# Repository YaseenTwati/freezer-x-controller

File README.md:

# Freezer X Controller

This project is a custom controller board built to replace the original controller of my freezer that stopped working. It is based on the Arduino Pro Micro and operates by reading the 10K NTC in the fridge and controlling the compressor relay.
**Note:** This controller *does not* replace the built-in compressor relay; instead, it uses an additional relay to control it.

[Dev Log Video](https://www.youtube.com/watch?v=zM9pKCJK8DQ)

**Disclaimer:** I do not recommend anyone build or use this as-is. Use it as a reference only. This was built for my specific use case, and it may or may not meet your needs.

<div style="display: flex; flex-direction: row; justify-content: space-around">

</div>

### Features:
- Interactive menu with configurable settings (target temp, dead time, max temp, hysteresis, etc.)
- Compressor dead time (minimum time the compressor must remain off before turning on again)
- Compressor overheating protection
- NTC short/disconnection handling (min/max temp)
- Raw SD card data logging
- Startup delay

### Important Notes:
1. **RTC Clock is disabled in the code**
   The RTC clock was originally intended to add real-time data to the logs. However, the IC used proved unreliable, so the RTC functionality was disabled in the code to save space.

2. **USB Serial / CDC**
   The USB CDC peripheral is disabled in the PlatformIO configuration to save flash storage space. This means `Serial.print()` cannot be used, **and the board needs to be manually reset during code uploads.**

   You can likely re-enable it now that the RTC is disabled, as there should be enough space available.

3. **SD Card Raw Data**
   Data is logged directly to the SD card without a filesystem by sending raw SPI commands. This approach was taken as an extreme storage-saving measure since most SD card libraries require too much space.
   [I wrote a blog post about this topic if you're interested](https://yaseen.ly/writing-data-to-sdcards-without-a-filesystem-spi/).

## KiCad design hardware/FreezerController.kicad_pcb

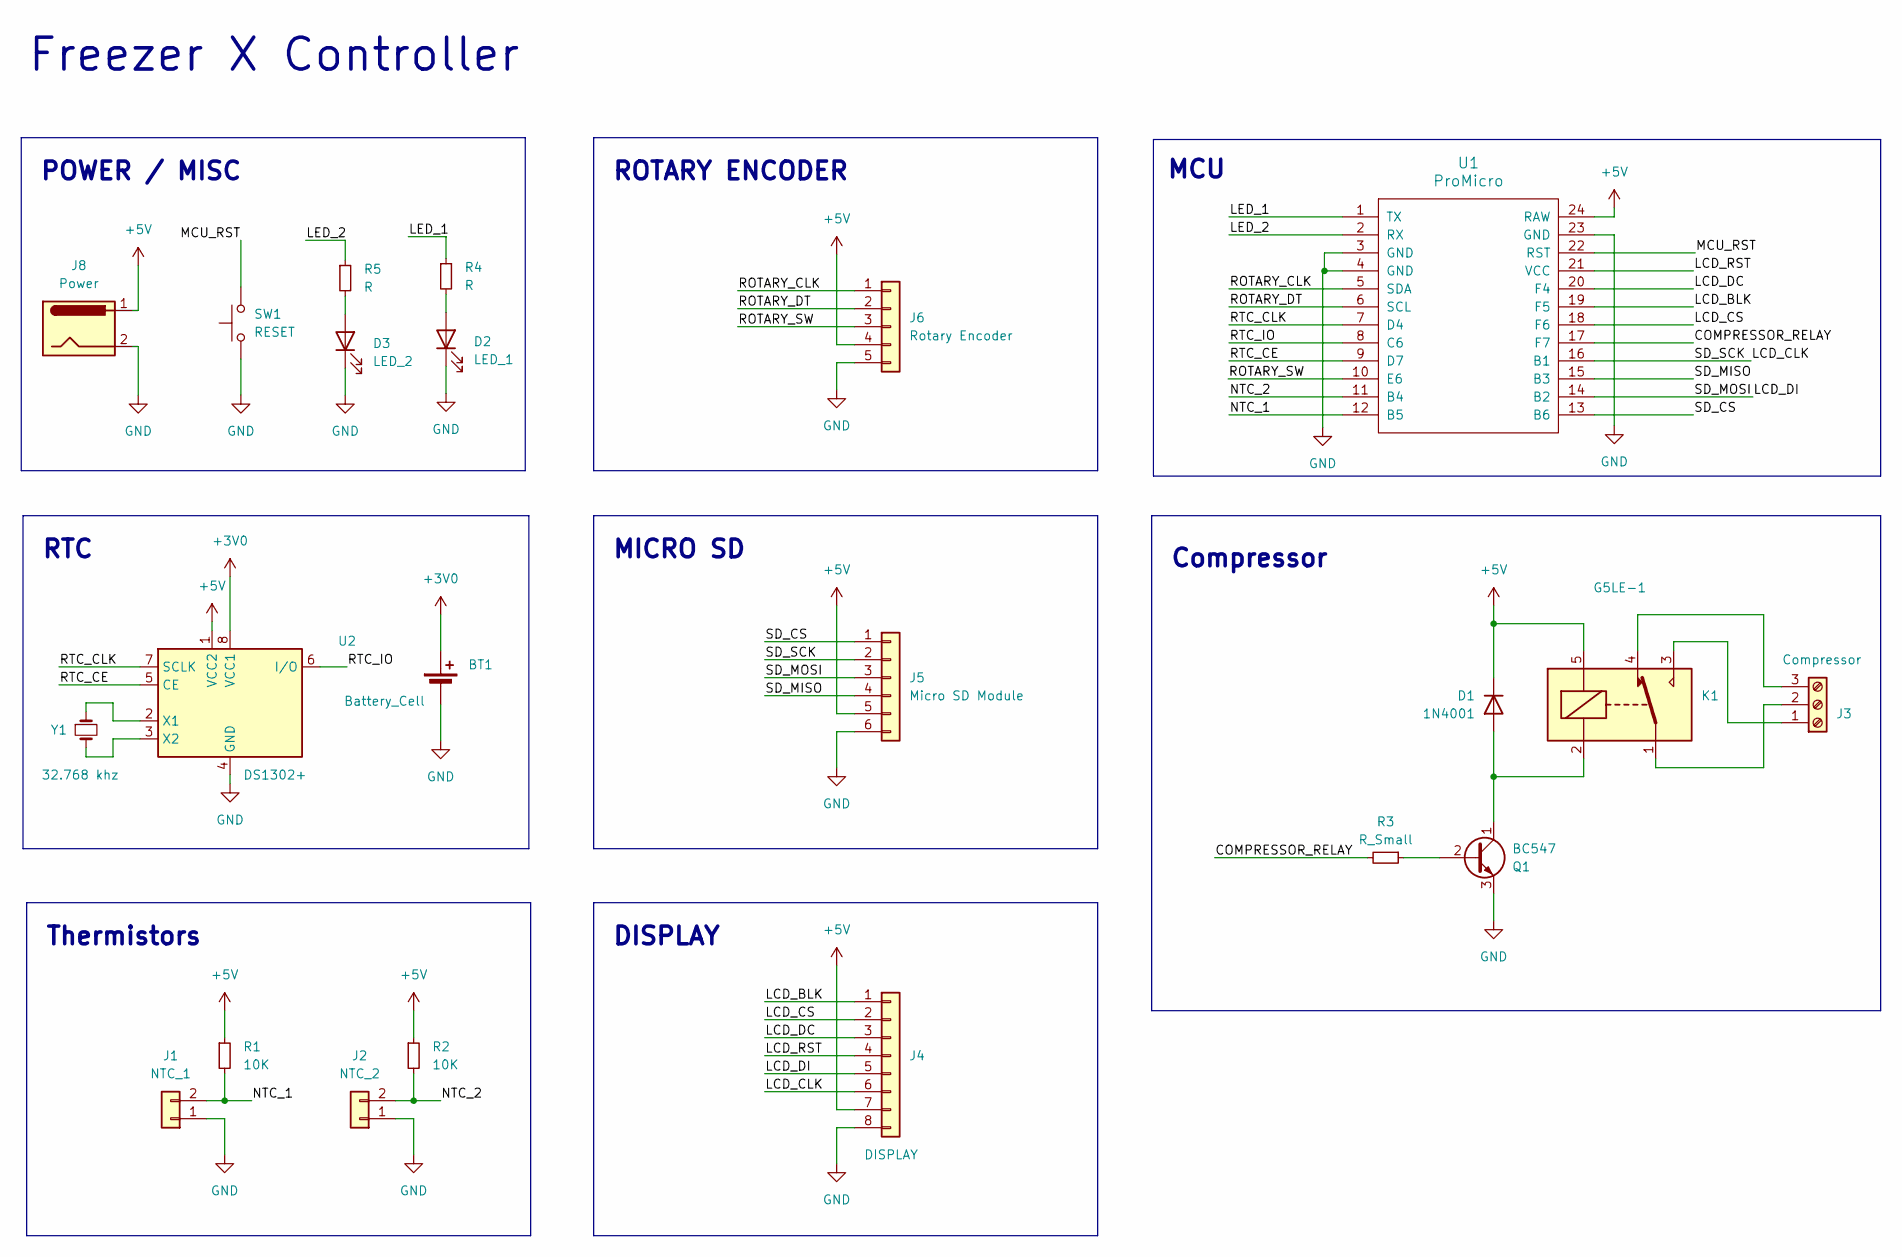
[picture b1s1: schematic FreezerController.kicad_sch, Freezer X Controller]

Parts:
BT1: Battery_Cell; BatteryHolder_Keystone_103_1x20mm
D1: 1N4001; D_DO-41_SOD81_P10.16mm_Horizontal
D2: LED_1; LED_D5.0mm
D3: LED_2; LED_D5.0mm
J1: NTC_1; PinHeader_1x02_P2.54mm_Vertical
J2: NTC_2; PinHeader_1x02_P2.54mm_Vertical
J3: Compressor; TerminalBlock_bornier-3_P5.08mm
J4: DISPLAY; PinHeader_1x08_P2.54mm_Vertical
J5: Micro SD Module; PinHeader_1x06_P2.54mm_Vertical
J6: Rotary Encoder; PinHeader_1x05_P2.54mm_Vertical
J8: Power; TerminalBlock_bornier-2_P5.08mm
K1: G5LE-1; Relay_SPDT_Omron-G5LE-1
Q1: BC547; TO-92L_HandSolder
R1, R2: 10K; R_Axial_DIN0207_L6.3mm_D2.5mm_P10.16mm_Horizontal
R3: R_Small; R_Axial_DIN0207_L6.3mm_D2.5mm_P10.16mm_Horizontal
R4, R5: R; R_Axial_DIN0309_L9.0mm_D3.2mm_P2.54mm_Vertical
SW1: RESET; SW_PUSH_6mm
U1: ProMicro
U2: DS1302+; DIP-8_W7.62mm
Y1: 32.768 khz; Crystal_AT310_D3.0mm_L10.0mm_Vertical

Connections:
+3V0: BT1.1 (+), U2.8 (VCC1)
+5V: D1.1 (K), J4.7, J5.5, J6.4, J8.1, K1.5, R1.1, R2.1, U1.24 (RAW), U2.1 (VCC2)
/COMPRESSOR_RELAY: R3.2, U1.17 (F7)
/LCD_BLK: J4.1, U1.19 (F5)
/LCD_CLK: J4.6, J5.2, U1.16 (B1)
/LCD_CS: J4.2, U1.18 (F6)
/LCD_DC: J4.3, U1.20 (F4)
/LCD_DI: J4.5, J5.3, U1.14 (B2)
/LCD_RST: J4.4, U1.21 (VCC)
/LED_1: R4.1, U1.1 (TX)
/LED_2: R5.1, U1.2 (RX)
/MCU_RST: SW1.2, U1.22 (RST)
/NTC_1: J1.2, R1.2, U1.12 (B5)
/NTC_2: J2.2, R2.2, U1.11 (B4)
/ROTARY_CLK: J6.1, U1.5 (SDA)
/ROTARY_DT: J6.2, U1.6 (SCL)
/ROTARY_SW: J6.3, U1.10 (E6)
/RTC_CE: U1.9 (D7), U2.5 (CE)
/RTC_CLK: U1.7 (D4), U2.7 (SCLK)
/RTC_IO: U1.8 (C6), U2.6 (I/O)
/SD_CS: J5.1, U1.13 (B6)
/SD_MISO: J5.4, U1.15 (B3)
GND: BT1.2 (-), D2.1 (K), D3.1 (K), J1.1, J2.1, J4.8, J5.6, J6.5, J8.2, Q1.3 (E), SW1.1, U1.3 (GND), U1.4 (GND), U1.23 (GND), U2.4 (GND)
unnamed: D1.2 (A), K1.2, Q1.1 (C)
unnamed: D2.2 (A), R4.2
unnamed: D3.2 (A), R5.2
unnamed: J3.1, K1.3
unnamed: J3.2, K1.1
unnamed: J3.3, K1.4
unnamed: Q1.2 (B), R3.1
unnamed: U2.2 (X1), Y1.1
unnamed: U2.3 (X2), Y1.2

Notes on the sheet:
Freezer X Controller
RTC
Compressor
ROTARY ENCODER
Thermistors
POWER / MISC
MCU
DISPLAY
MICRO SD

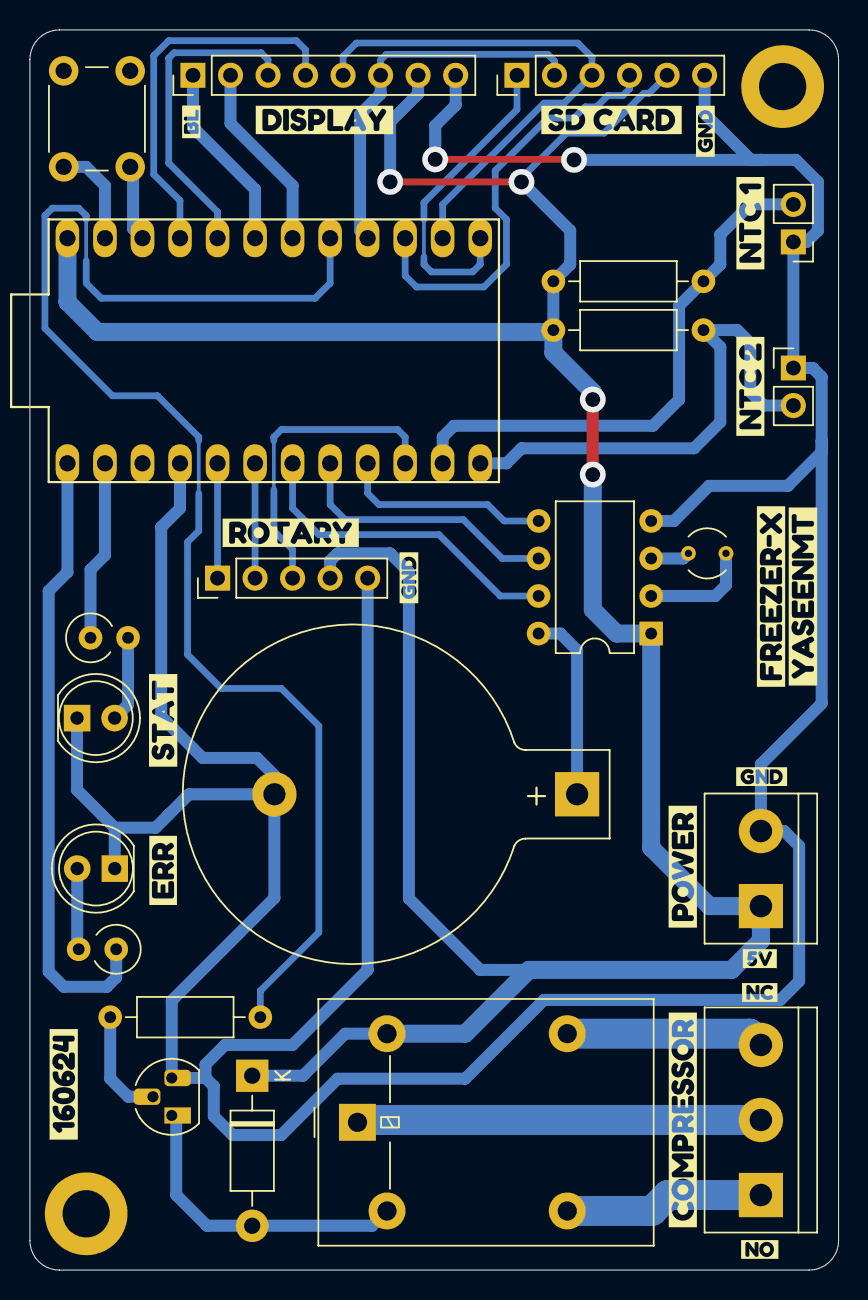
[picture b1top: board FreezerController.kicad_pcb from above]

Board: 2 copper layers, 54.7 x 83.9 mm, 41 parts (0 on the bottom side), 32 nets.

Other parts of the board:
kibuzzard-666E3AD2: G***; kibuzzard-666E3AD2
kibuzzard-666E34B9: G***; kibuzzard-666E34B9
kibuzzard-666E34CF: G***; kibuzzard-666E34CF
kibuzzard-666E34E6: G***; kibuzzard-666E34E6
kibuzzard-666E35C1, kibuzzard-666E35C1#2, kibuzzard-666E35C1#3: G***; kibuzzard-666E35C1
kibuzzard-666E35CE: G***; kibuzzard-666E35CE
kibuzzard-666E35DE: G***; kibuzzard-666E35DE
kibuzzard-666E35EC: G***; kibuzzard-666E35EC
kibuzzard-666E38E3: G***; kibuzzard-666E38E3
kibuzzard-666E343D: G***; kibuzzard-666E343D
kibuzzard-666E346F: G***; kibuzzard-666E346F
kibuzzard-666E349B: G***; kibuzzard-666E349B
kibuzzard-666E394F: G***; kibuzzard-666E394F
kibuzzard-666E3446: G***; kibuzzard-666E3446
kibuzzard-666E3626: G***; kibuzzard-666E3626
kibuzzard-666E3888: G***; kibuzzard-666E3888
kibuzzard-666E3893: G***; kibuzzard-666E3893

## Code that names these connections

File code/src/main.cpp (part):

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const int THERMISTOR_2_PIN = A9;

//// RTC
const int RTC_CLK = 4;
const int RTC_IO = 5;
const int RTC_CE = 6;

// Rotary Encoder
const int ROTARY_CLK = 2;
const int ROTARY_DT = 3;
const int ROTARY_SW = 7;

// LCD
const int LCD_RST = 20;
const int LCD_DC = 21;
const int LCD_DIN = 16;
const int LCD_SCK = 15;
const int LCD_CS = 19;

// Micro SD
const int MICRO_SD_CS = 10;
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const int MICRO_SD_SCK = 15;

// Compressor Relay
const int COMPRESSOR_RELAY = 18;

// LEDs
const int BLUE_LED_PIN = 0;
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{
  // Serial.println("initialize_compressor()");

  pinMode(COMPRESSOR_RELAY, OUTPUT);
  digitalWrite(COMPRESSOR_RELAY, LOW);
}

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{
  // Serial.println("initialize_input()");

  pinMode(ROTARY_SW, INPUT_PULLUP);
  attachInterrupt(digitalPinToInterrupt(ROTARY_SW), on_button_pressed, RISING);
}

void initialize_watchdog()
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
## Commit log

2024-12-13 add project files
2024-12-13 Add LICENSE
